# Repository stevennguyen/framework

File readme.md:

# 7c8 Framework

Framework is a 5x12 ortholinear keyboard featuring:

* All through-hole components (except Kailh hotswap sockets)
* QMK firmware with VIA support
* Rotary encoder
* Hotswappable switches
* FR-4 and acrylic sandwich construction
* USB Type-C
* MIT (one 2u), grid (two 1u), and two 2u, bottom row configuration

## Info

### Discord

https://discord.gg/MpxnD9PygN

### License

Framework is licensed under [CC BY-NC-SA 4.0](https://creativecommons.org/licenses/by-nc-sa/4.0/). Please modify my design to make a keyboard that fits you!

### Revisions

**rev0** is an early prototype/proof of concept  
**rev1** is the current revision and should be used for fabrication or modification

### General

The ATmega328P does not come with a USB bootloader from factory. You will need to flash the chip with a bootloader through the ISP header first. You can find a pre-compiled .hex to flash at [USBaspLoader/bootloader.hex](USBaspLoader/bootloader.hex), or compile your own using the documentation found in the [USBaspLoader/](USBaspLoader/) folder. Everything has been preconfigured for use with the Framework.

[USBaspLoader](https://github.com/baerwolf/USBaspLoader) is a project maintained by [Stephan Baerwolf](https://github.com/baerwolf).

Fuse bytes should be:
* lfuse = 0xd7
* hfuse = 0xd0
* efuse = 0x04

After [setting up your QMK environment](https://docs.qmk.fm/#/newbs_getting_started), flash the Framework firmware:

```
make 7c8/framework:default:flash # default keymap
make 7c8/framework:via:flash     # via-compatible keymap
```

Alternatively, a precompiled .hex with bootloader and Framework QMK firmware with VIA support can be found at [firmware/bl_framework_via.hex](firmware/bl_framework_via.hex). Flashing/fusing with avrdude looks like this:

```
avrdude -c <programmer> -p atmega328p -U flash:w:bl_framework_via.hex:i -U lfuse:w:0xd7:m -U hfuse:w:0xd0:m -U efuse:w:0x04:m
```

### Layout

Framework supports MIT, grid, and 2x2u spacebar layouts. Refer to [framework.h](https://github.com/qmk/qmk_firmware/blob/master/keyboards/7c8/framework/framework.h). Layout options are also configurable in VIA.

### Physical construction

Please see [this separate note on physical construction](doc/physical_construction.md).

### Build guide

Please see the [build guide](doc/build_guide) for more information.

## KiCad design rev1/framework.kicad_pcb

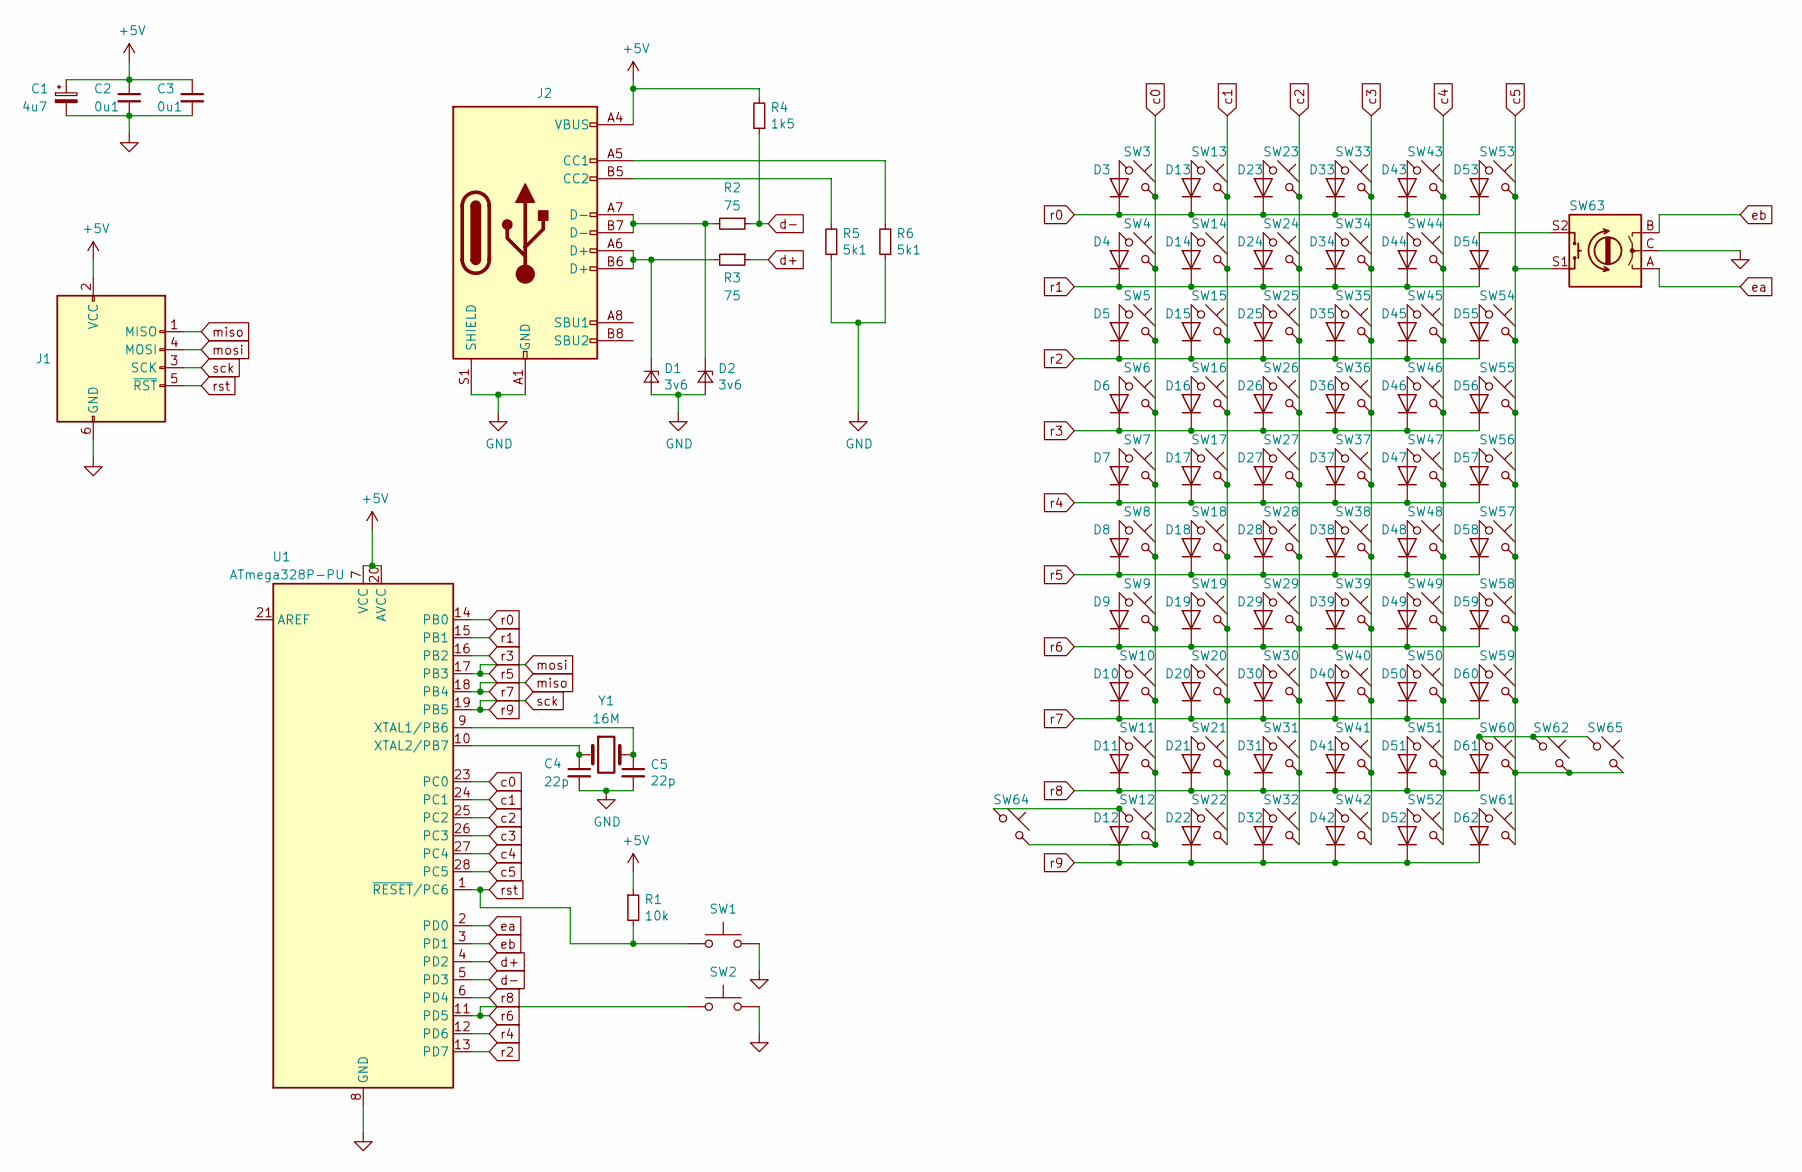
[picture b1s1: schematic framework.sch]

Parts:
C1: 4u7; CP_Radial_D4.0mm_P1.50mm
C2, C3: 0u1; C_Axial_L3.8mm_D2.6mm_P7.50mm_Horizontal
C4, C5: 22p; C_Axial_L3.8mm_D2.6mm_P7.50mm_Horizontal
D1, D2: 3v6; D_DO-35_SOD27_P7.62mm_Horizontal
D3, D4, D5, D6, D7, D8, D9, D10, D11, D12, D13, D14, D15, D16, D17, D18, D19, D20, D21, D22, D23, D24, D25, D26, D27, D28, D29, D30, D31, D32, D33, D34, D35, D36, D37, D38, D39, D40, D41, D42, D43, D44, D45, D46, D47, D48, D49, D50, D51, D52, D53, D54, D55, D56, D57, D58, D59, D60, D61, D62: D; D_DO-35_SOD27_P7.62mm_Horizontal
J1: AVR-ISP-6; PinHeader_2x03_P2.54mm_Vertical
J2: USB_C_Receptacle_USB2.0; USB_C_Receptacle_GCT_USB4085
R1: 10k; R_Axial_DIN0204_L3.6mm_D1.6mm_P5.08mm_Horizontal
R2, R3: 75; R_Axial_DIN0204_L3.6mm_D1.6mm_P5.08mm_Horizontal
R4: 1k5; R_Axial_DIN0207_L6.3mm_D2.5mm_P7.62mm_Horizontal
R5, R6: 5k1; R_Axial_DIN0204_L3.6mm_D1.6mm_P5.08mm_Horizontal
SW1, SW2: SW_Push; SW_PUSH_6mm_H4.3mm
SW3, SW4, SW5, SW6, SW7, SW8, SW9, SW10, SW11, SW12, SW13, SW14, SW15, SW16, SW17, SW18, SW19, SW20, SW21, SW22, SW23, SW24, SW25, SW26, SW27, SW28, SW29, SW30, SW31, SW32, SW33, SW34, SW35, SW36, SW37, SW38, SW39, SW40, SW41, SW42, SW43, SW44, SW45, SW46, SW47, SW48, SW49, SW50, SW51, SW52, SW53, SW54, SW55, SW56, SW57, SW58, SW59, SW60, SW61, SW62, SW64, SW65: SW_Push_45deg; Kailh_socket_MX_no_fsilk
SW63: Rotary_Encoder_Switch; RotaryEncoder_Alps_EC11E-Switch_Vertical_H20mm
U1: ATmega328P-PU; DIP-28_W7.62mm
Y1: 16M; Crystal_HC49-4H_Vertical

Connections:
+5V: C1.1, C2.1, C3.1, J1.2 (VCC), J2.A4 (VBUS), J2.A9 (VBUS), J2.B4 (VBUS), J2.B9 (VBUS), R1.1, R4.2, U1.7 (VCC), U1.20 (AVCC)
GND: C1.2, C2.2, C3.2, C4.2, C5.2, D1.2 (A), D2.2 (A), J1.6 (GND), J2.A1 (GND), J2.A12 (GND), J2.B1 (GND), J2.B12 (GND), J2.S1 (SHIELD), R5.1, R6.1, SW1.2, SW2.2, SW63.C, U1.8 (GND), U1.22 (GND)
unnamed: C4.1, U1.10 (XTAL2/PB7), Y1.1
unnamed: C5.1, U1.9 (XTAL1/PB6), Y1.2
unnamed: D1.1 (K), J2.A6 (D+), J2.B6 (D+), R3.2
unnamed: D2.1 (K), J2.A7 (D-), J2.B7 (D-), R2.2
unnamed: D3.2 (A), SW3.1
unnamed: D4.2 (A), SW4.1
unnamed: D5.2 (A), SW5.1
unnamed: D6.2 (A), SW6.1
unnamed: D7.2 (A), SW7.1
unnamed: D8.2 (A), SW8.1
unnamed: D9.2 (A), SW9.1
unnamed: D10.2 (A), SW10.1
unnamed: D11.2 (A), SW11.1
unnamed: D12.2 (A), SW12.1, SW64.1
unnamed: D13.2 (A), SW13.1
unnamed: D14.2 (A), SW14.1
unnamed: D15.2 (A), SW15.1
unnamed: D16.2 (A), SW16.1
unnamed: D17.2 (A), SW17.1
unnamed: D18.2 (A), SW18.1
unnamed: D19.2 (A), SW19.1
unnamed: D20.2 (A), SW20.1
unnamed: D21.2 (A), SW21.1
unnamed: D22.2 (A), SW22.1
unnamed: D23.2 (A), SW23.1
unnamed: D24.2 (A), SW24.1
unnamed: D25.2 (A), SW25.1
unnamed: D26.2 (A), SW26.1
unnamed: D27.2 (A), SW27.1
unnamed: D28.2 (A), SW28.1
unnamed: D29.2 (A), SW29.1
unnamed: D30.2 (A), SW30.1
unnamed: D31.2 (A), SW31.1
unnamed: D32.2 (A), SW32.1
unnamed: D33.2 (A), SW33.1
unnamed: D34.2 (A), SW34.1
unnamed: D35.2 (A), SW35.1
unnamed: D36.2 (A), SW36.1
unnamed: D37.2 (A), SW37.1
unnamed: D38.2 (A), SW38.1
unnamed: D39.2 (A), SW39.1
unnamed: D40.2 (A), SW40.1
unnamed: D41.2 (A), SW41.1
unnamed: D42.2 (A), SW42.1
unnamed: D43.2 (A), SW43.1
unnamed: D44.2 (A), SW44.1
unnamed: D45.2 (A), SW45.1
unnamed: D46.2 (A), SW46.1
unnamed: D47.2 (A), SW47.1
unnamed: D48.2 (A), SW48.1
unnamed: D49.2 (A), SW49.1
unnamed: D50.2 (A), SW50.1
unnamed: D51.2 (A), SW51.1
unnamed: D52.2 (A), SW52.1
unnamed: D53.2 (A), SW53.1
unnamed: D54.2 (A), SW63.S2
unnamed: D55.2 (A), SW54.1
unnamed: D56.2 (A), SW55.1
unnamed: D57.2 (A), SW56.1
unnamed: D58.2 (A), SW57.1
unnamed: D59.2 (A), SW58.1
unnamed: D60.2 (A), SW59.1
unnamed: D61.2 (A), SW60.1, SW62.1, SW65.1
unnamed: D62.2 (A), SW61.1
unnamed: J2.A5 (CC1), R6.2
unnamed: J2.B5 (CC2), R5.2
c0: SW3.2, SW4.2, SW5.2, SW6.2, SW7.2, SW8.2, SW9.2, SW10.2, SW11.2, SW12.2, SW64.2, U1.23 (PC0)
c1: SW13.2, SW14.2, SW15.2, SW16.2, SW17.2, SW18.2, SW19.2, SW20.2, SW21.2, SW22.2, U1.24 (PC1)
c2: SW23.2, SW24.2, SW25.2, SW26.2, SW27.2, SW28.2, SW29.2, SW30.2, SW31.2, SW32.2, U1.25 (PC2)
c3: SW33.2, SW34.2, SW35.2, SW36.2, SW37.2, SW38.2, SW39.2, SW40.2, SW41.2, SW42.2, U1.26 (PC3)
c4: SW43.2, SW44.2, SW45.2, SW46.2, SW47.2, SW48.2, SW49.2, SW50.2, SW51.2, SW52.2, U1.27 (PC4)
c5: SW53.2, SW54.2, SW55.2, SW56.2, SW57.2, SW58.2, SW59.2, SW60.2, SW61.2, SW62.2, SW63.S1, SW65.2, U1.28 (PC5)
d+: R3.1, U1.4 (PD2)
d-: R2.1, R4.1, U1.5 (PD3)
ea: SW63.A, U1.2 (PD0)
eb: SW63.B, U1.3 (PD1)
miso: D10.1 (K), D20.1 (K), D30.1 (K), D40.1 (K), D50.1 (K), D60.1 (K), J1.1 (MISO), U1.18 (PB4)
mosi: D8.1 (K), D18.1 (K), D28.1 (K), D38.1 (K), D48.1 (K), D58.1 (K), J1.4 (MOSI), U1.17 (PB3)
r0: D3.1 (K), D13.1 (K), D23.1 (K), D33.1 (K), D43.1 (K), D53.1 (K), U1.14 (PB0)
r1: D4.1 (K), D14.1 (K), D24.1 (K), D34.1 (K), D44.1 (K), D54.1 (K), U1.15 (PB1)
r2: D5.1 (K), D15.1 (K), D25.1 (K), D35.1 (K), D45.1 (K), D55.1 (K), U1.13 (PD7)
r3: D6.1 (K), D16.1 (K), D26.1 (K), D36.1 (K), D46.1 (K), D56.1 (K), U1.16 (PB2)
r4: D7.1 (K), D17.1 (K), D27.1 (K), D37.1 (K), D47.1 (K), D57.1 (K), U1.12 (PD6)
r6: D9.1 (K), D19.1 (K), D29.1 (K), D39.1 (K), D49.1 (K), D59.1 (K), SW2.1, U1.11 (PD5)
r8: D11.1 (K), D21.1 (K), D31.1 (K), D41.1 (K), D51.1 (K), D61.1 (K), U1.6 (PD4)
r9: D12.1 (K), D22.1 (K), D32.1 (K), D42.1 (K), D52.1 (K), D62.1 (K), J1.3 (SCK), U1.19 (PB5)
rst: J1.5 (~RST), R1.2, SW1.1, U1.1 (~RESET~/PC6)

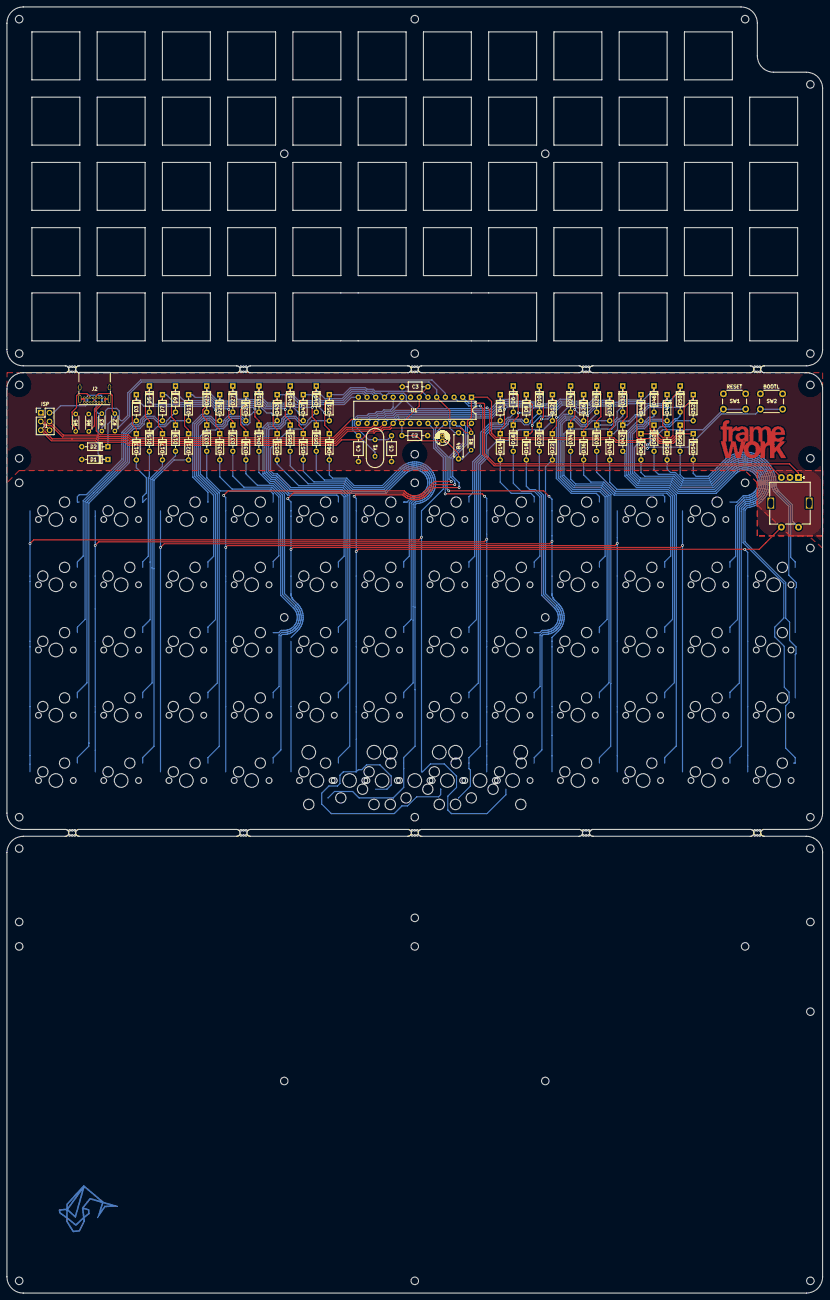
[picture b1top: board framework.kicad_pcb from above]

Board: 2 copper layers, 238.1 x 375.5 mm, 152 parts (0 on the bottom side), 89 nets.

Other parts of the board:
mouse-bite-2mm-slot, mouse-bite-2mm-slot#2, mouse-bite-2mm-slot#3, mouse-bite-2mm-slot#4, mouse-bite-2mm-slot#5, mouse-bite-2mm-slot#6, mouse-bite-2mm-slot#7, mouse-bite-2mm-slot#8, mouse-bite-2mm-slot#9, mouse-bite-2mm-slot#10: VAL**; mouse-bite-2mm-slot

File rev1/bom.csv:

"Id";"Designator";"Package";"Quantity";"Designation";"Supplier and ref";
1;"C1";"CP_Radial_D4.0mm_P1.50mm";1;"4u7";;;
2;"G***";"framework_rev1";1;"LOGO";;;
3;"G***";"7c8stevennguyen";1;"LOGO";;;
4;"Y1";"Crystal_HC49-4H_Vertical";1;"16M";;;
5;"U1";"DIP-28_W7.62mm";1;"ATmega328P-PU";;;
6;"SW65,SW64,SW62,SW61,SW60,SW59,SW58,SW57,SW56,SW55,SW54,SW53,SW52,SW51,SW50,SW49,SW48,SW47,SW46,SW45,SW44,SW43,SW42,SW41,SW40,SW39,SW38,SW37,SW36,SW35,SW34,SW33,SW32,SW31,SW30,SW29,SW28,SW27,SW26,SW25,SW24,SW23,SW22,SW21,SW20,SW19,SW18,SW17,SW16,SW15,SW14,SW13,SW12,SW11,SW10,SW9,SW8,SW7,SW6,SW5,SW4,SW3";"Kailh_socket_MX_no_fsilk";62;"SW_Push_45deg";;;
7;"SW63";"RotaryEncoder_Alps_EC11E-Switch_Vertical_H20mm";1;"Rotary_Encoder_Switch";;;
8;"SW2,SW1";"SW_PUSH_6mm_H4.3mm";2;"SW_Push";;;
9;"R6,R5";"R_Axial_DIN0204_L3.6mm_D1.6mm_P5.08mm_Horizontal";2;"5k1";;;
10;"R4";"R_Axial_DIN0207_L6.3mm_D2.5mm_P7.62mm_Horizontal";1;"1k5";;;
11;"R3,R2";"R_Axial_DIN0204_L3.6mm_D1.6mm_P5.08mm_Horizontal";2;"75";;;
12;"R1";"R_Axial_DIN0204_L3.6mm_D1.6mm_P5.08mm_Horizontal";1;"10k";;;
13;"J2";"USB_C_Receptacle_GCT_USB4085";1;"USB_C_Receptacle_USB2.0";;;
14;"J1";"PinHeader_2x03_P2.54mm_Vertical";1;"AVR-ISP-6";;;
15;"D62,D61,D60,D59,D58,D57,D56,D55,D54,D53,D52,D51,D50,D49,D48,D47,D46,D45,D44,D43,D42,D41,D40,D39,D38,D37,D36,D35,D34,D33,D32,D31,D30,D29,D28,D27,D26,D25,D24,D23,D22,D21,D20,D19,D18,D17,D16,D15,D14,D13,D12,D11,D10,D9,D8,D7,D6,D5,D4,D3";"D_DO-35_SOD27_P7.62mm_Horizontal";60;"D";;;
16;"D2,D1";"D_DO-35_SOD27_P7.62mm_Horizontal";2;"3v6";;;
17;"C5,C4";"C_Axial_L3.8mm_D2.6mm_P7.50mm_Horizontal";2;"22p";;;
18;"C3,C2";"C_Axial_L3.8mm_D2.6mm_P7.50mm_Horizontal";2;"0u1";;;
19;"G***";"framework";1;"LOGO";;;
20;"REF**,REF**,REF**,REF**,REF**,REF**,REF**,REF**,REF**,REF**,REF**,REF**,REF**,REF**,REF**,REF**,REF**,REF**,REF**,REF**,REF**,REF**,REF**,REF**,REF**,REF**,REF**,REF**,REF**,REF**,REF**";"MountingHole_2.2mm_M2";31;"MountingHole_2.2mm_M2";;;
21;"REF**,REF**,REF**";"Stabilizer_MX_2u";3;"Stabilizer_MX_2u";;;
22;"G***";"keyswitch";1;"LOGO";;;
23;"mouse-bite-2mm-slot,mouse-bite-2mm-slot,mouse-bite-2mm-slot,mouse-bite-2mm-slot,mouse-bite-2mm-slot,mouse-bite-2mm-slot,mouse-bite-2mm-slot,mouse-bite-2mm-slot,mouse-bite-2mm-slot,mouse-bite-2mm-slot";"mouse-bite-2mm-slot";10;"VAL**";;;

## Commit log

2021-01-17 hello world
2021-01-17 remove qmk/ from .gitignore
2021-01-17 Add layout info to readme.md
2021-01-17 Update keyboard layout image
2021-01-17 Added .pdf schematic for rev. 1 + readme tweaks
2021-01-20 add more images
2021-01-25 Fix mixed up MOSI and MISO connections for ISP
2021-01-25 correct efuse byte in readme.md
2021-01-26 add acrylic cover + update schematic pdf
2021-01-26 update gerbers
2021-01-26 Dimension acrylic
2021-02-07 board aesthetic changes
2021-02-21 Update images
2021-02-28 Documentation changes
2021-02-28 documentation clarification
2021-02-28 Flashing information
2021-03-03 move fish logo slightly
2021-03-19 capitalization ting
2021-04-30 uncapitalization ting + gitignore qmk/
2021-04-30 re-index for .gitignore
2021-08-12 correct schematic: schottky to zener diode symbols on USB d+/d-
2021-08-12 changed schematic, schottky to zener diode symbol on USB d+/d-
2021-08-12 remove redundant info
    link to physical construction details in readme.md
2021-08-12 update file reference links
2021-08-21 add discord link
2021-08-23 clean up acrylic shield .kicad-pcb file + add .step export
2021-08-23 fix mounting hole misalignment on backplate
2021-08-23 fix .step export for misaligned backplate hole
2021-08-23 add images
2021-08-23 change readme.md title image
2021-08-23 fix render image file extensions
2021-08-23 change images again
2021-09-11 file rename + cleanup
2021-09-11 construction documentation update
2021-09-28 Add standard component name for Bill of Materials
    Added standard component names for Bill of Materials for easier reference and lookup.
2021-10-01 Format @potateros addition to physical_construction.md
2021-11-30 fix framework.h link
2021-12-06 add build guide
2021-12-08 add usb c soldering video reference
2022-01-11 add build note, fix build guide typo
2022-03-19 add files for 3d printing and manufacturing sandwich case layers
2022-07-06 change efuse from 0xfc to 0x04 to suppress verification error
2022-07-09 rename directory rev1/acrylic -> rev1/dxf_layers; update rev1/3d_layers/bottom.* to include mounting points for acrylic shield
2023-02-08 Fix QMK link in readme.md
